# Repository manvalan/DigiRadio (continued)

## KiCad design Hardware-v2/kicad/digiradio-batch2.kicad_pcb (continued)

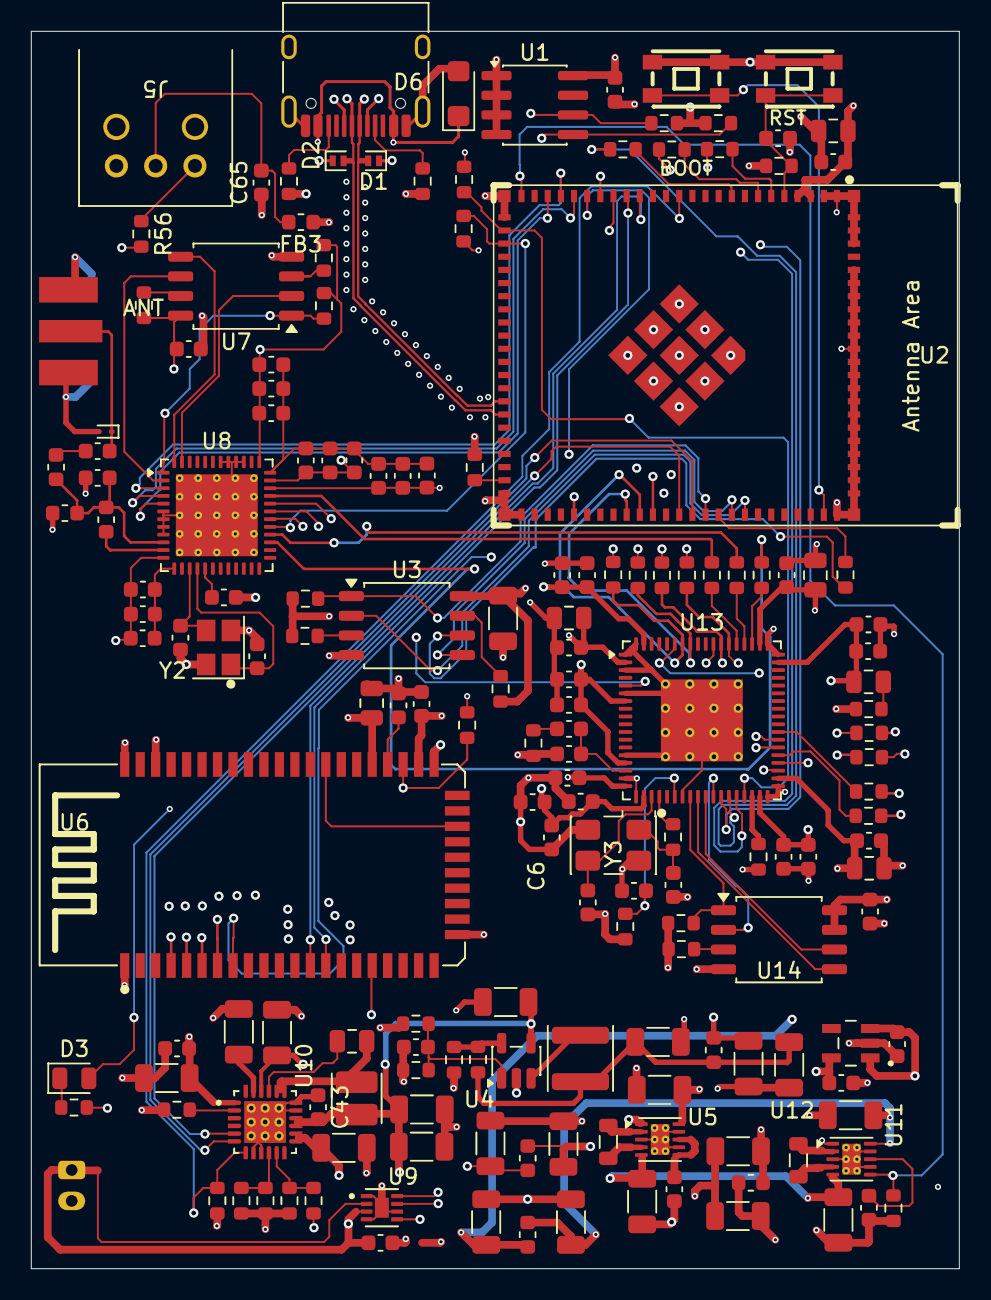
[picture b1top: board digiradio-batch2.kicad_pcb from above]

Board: 6 copper layers, 60.0 x 80.0 mm, 171 parts (1 on the bottom side), 119 nets.

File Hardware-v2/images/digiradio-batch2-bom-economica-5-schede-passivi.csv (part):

Riferimenti;Valore;Qta scheda;Qta necessaria;Stato;Fornitore;Codice;MPN scelto;Marca;Package;Stock;Pezzi da comprare;Prezzo unit EUR;Costo EUR;Costo originale EUR;Consegna;MPN schema;Impronta;Note;Opzioni da verificare
C1,C4,C15-C17,C19,C25,C32,C38,C44-C50,C54,C62-C65;100nF;21;105;Sostituito;LCSC;C282519;TCC0603X7R104K500CT;CCTC;0603;1010040;120;0,0055;0,6660;1,1099;;CC0603KRX7R9BB104;Capacitor_SMD:C_0603_1608Metric;;
C2,C6,C10,C24,C28,C31,C36,C37,C56,C57;1uF;10;50;Originale;LCSC;C5199872;CL10B105KB8NQNC;Samsung Electro-Mechanics;0603;2383870;50;0,0214;1,0696;1,0696;;CL10B105KB8NQNC;Capacitor_SMD:C_0603_1608Metric;;
C3;22uF;1;5;Sostituito;LCSC;C92814;LMK212BJ226MG-T;Taiyo Yuden;0805;6510;5;0,1156;0,5782;1,6756;;GRM21BZ71A226ME15L;Capacitor_SMD:C_0805_2012Metric;Su 3V3_DIGITAL. Gli alternativi sono X5R invece di X7R, che a 3,3 V va bene.;
C5,C9,C11,C12,C14,C42,C52,C55,C73-C76,C80,C83,C84;10uF;15;75;Sostituito;LCSC;C105482;1206X106K250NT;FH;1206;45370;80;0,0638;5,1056;15,2667;;CL31A106KBHNNNE;Capacitor_SMD:C_1206_3216Metric;Da 50 V a 25 V negli alternativi. La tensione più alta sulla riga è V_USB/PMID, 5 V.;
C8,C13,C33,C53;4.7uF;4;20;Sostituito;LCSC;C1872;CL31B475KAHNNNE;Samsung Electro-Mechanics;1206;60905;20;0,0577;1,1547;1,2621;;1206B475K500NT;Capacitor_SMD:C_1206_3216Metric;Da 50 V a 25 V con CL31B475KAHNNNE. La riga lavora su VSYS e REGN, massimo 5 V.;
C18,C58-C61;10uF;5;25;Sostituito;LCSC;C15850;CL21A106KAYNNNE;Samsung Electro-Mechanics;0805;1517320;40;0,0395;1,5789;2,1728;;GRM21BR61E106KA73L;Capacitor_SMD:C_0805_2012Metric;;
C20;33pF;1;5;Originale;LCSC;C913596;GQM1875C2E330JB12D;muRata;0603;790;5;0,1305;0,6525;0,6525;;GQM1875C2E330JB12D;Capacitor_SMD:C_0603_1608Metric;Rete di adattamento dell'antenna del Si4684: tengo il Murata ad alto Q, il risparmio è di centesimi.;C1663: C0G standard 50 V, Q più basso
C21,C26,C29,C34;8.2pF;4;20;Sostituito;LCSC;C376804;TCC0603COG8R2C500CT;CCTC;0603;1700;100;0,0038;0,3759;1,5217;;CC0603JRNPO9BN8R2;Capacitor_SMD:C_0603_1608Metric;;
C22;2.7pF;1;5;Originale;LCSC;C2178971;GQM1875C2E2R7BB12D;muRata;0603;1295;5;0,1421;0,7107;0,7107;;GQM1875C2E2R7BB12D;Capacitor_SMD:C_0603_1608Metric;Rete di adattamento dell'antenna del Si4684, tolleranza ±0,1 pF: tengo il Murata.;
C23,C27,C30,C35;2.2nF;4;20;Originale;LCSC;C16033;CL10B222KB8NNNC;Samsung Electro-Mechanics;0603;130050;50;0,0089;0,4431;0,4431;;CL10B222KB8NNNC;Capacitor_SMD:C_0603_1608Metric;;
C39;1nF;1;5;Sostituito;LCSC;C1588;CL10B102KB8NNNC;Samsung Electro-Mechanics;0603;1150850;50;0,0089;0,4431;0,7832;;GRM188R71H102KA01D;Capacitor_SMD:C_0603_1608Metric;;
C43;10uF;1;5;Sostituito;LCSC;C77044;GRM188R61A106KE69D;muRata;0603;198760;10;0,0306;0,3061;0,3831;;CL10A106KP8NNNC;Capacitor_SMD:C_0603_1608Metric;;
C51;47nF;1;5;Sostituito;LCSC;C282770;TCC0805X7R473K500DT;CCTC;0805;3400;50;0,0088;0,4386;0,7709;;CL21B473KBCNNNC;Capacitor_SMD:C_0805_2012Metric;Bootstrap del BQ25896. L'originale ha stock LCSC a zero.;
C67-C70;10nF;4;20;Originale;LCSC;C100042;CC0603KRX7R9BB103;YAGEO;0603;4000;100;0,0046;0,4565;0,4565;;CC0603KRX7R9BB103;Capacitor_SMD:C_0603_1608Metric;;
C79,C85;22uF;2;10;Sostituito;LCSC;C1859;1206X226K100NT;FH;1206;73980;10;0,1622;1,6219;2,1303;;CL31A226KAHNNNE;Capacitor_SMD:C_1206_3216Metric;Da 25 V a 10 V con 1206X226K100NT. La riga lavora sul lato 1,2 V.;
C81;150pF;1;5;Originale;LCSC;C107038;CC0603JRNPO9BN151;YAGEO;0603;328700;100;0,0046;0,4565;0,4565;;CC0603JRNPO9BN151;Capacitor_SMD:C_0603_1608Metric;;
C82;5.6nF;1;5;Sostituito;LCSC;C282685;TCC0603X7R562K500CT;CCTC;0603;4800;100;0,0030;0,3043;0,4475;;CC0603KRX7R9BB562;Capacitor_SMD:C_0603_1608Metric;;
C139-C142;12pF;4;20;Originale;LCSC;C107034;CC0603JRNPO9BN120;YAGEO;0603;1915200;100;0,0055;0,5550;0,5550;;CC0603JRNPO9BN120;Capacitor_SMD:C_0603_1608Metric;;
FB1-FB5;BLM18SG121TN1D;5;25;Sostituito;LCSC;C52178221;PBBHAQ1608H-121T30;PROD Tech;0603;4700;40;0,0215;0,8604;1,7633;;BLM18SG121TN1D;Inductor_SMD:L_0603_1608Metric;PROD Tech: stesso 120 Ω a 100 MHz e 3 A, DCR 50 mΩ contro 25 mΩ. Conviene solo da qualche scheda in su per il minimo d'ordine di 20.;
L1;18nH;1;5;Originale;LCSC;C113263;LQW18AN18NJ00D;muRata;0603;26020;10;0,0458;0,4583;0,4583;;LQW18AN18NJ00D;Inductor_SMD:L_0603_1608Metric;Rete RF del Si4684: tengo il Murata.;C6807995: APV AHW1608C-18NJTF, simile, Q 35
L2;120nH;1;5;Originale;LCSC;C341697;LQW18ANR12J00D;muRata;0603;105;5;0,1578;0,7890;0,7890;;LQW18ANR12J00D;Inductor_SMD:L_0603_1608Metric;Rete RF del Si4684: tengo il Murata. Stock LCSC basso.;C6364700: APV AHW1608C-R12JTF, simile, Q 32, SRF 1,3 GHz
L3;22nH;1;5;Sostituito;LCSC;C84341;LQW18AN22NG00D;muRata;0603;4230;10;0,0559;0,5594;0,5594;;LQW18AN22NH00D;Inductor_SMD:L_0603_1608Metric;L'originale ±3% non è a catalogo LCSC: uso la stessa serie Murata a ±2%.;
L4,L6;1.5uH;2;10;Originale;LCSC;C54421974;HPLA-201210-1R5-M;YOUCHI;0805;5980;20;0,0331;0,6616;0,6616;;HPLA-201210-1R5-M;Inductor_SMD:L_0805_2012Metric;;
L5;1uH;1;5;Originale;LCSC;C280505;LVF303015-1R0T-N;Chilisin;SMD,3x3mm;1600;10;0,0541;0,5406;0,5406;;LVF303015-1R0T-N;Inductor_SMD:L_Cenker_CKCS3015;;
L7;2.2uH;1;5;Sostituito;LCSC;C7427099;ANR4018T2R2M;APV;SMD,4x4mm;5230;10;0,0407;0,4073;0,4073;;SDER041H-2R2MS;Inductor_SMD:L_APV_ANR4018;L'originale Cyntec non è più acquistabile. APV ANR4018T2R2M è l'impronta già sul PCB: 2,6 A nominali e 3,2 A di saturazione, abbondanti per il buck da 1 A TLV62568.;
R1,R5,R9-R11,R14,R15,R17-R24,R26,R29,R31,R32,R34,R35,R54;10K;22;110;Sostituito;LCSC;C25804;0603WAF1002T5E;UNI-ROYAL;0603;3260200;200;0,0020;0,3938;0,4834;;RC0603FR-0710KL;Resistor_SMD:R_0603_1608Metric;;
R2,R3;5.1K;2;10;Sostituito;LCSC;C23186;0603WAF5101T5E;UNI-ROYAL;0603;16131200;100;0,0014;0,1432;0,1531;;FRC0603F5101TS;Resistor_SMD:R_0603_1608Metric;;
R7,R8;2.2K;2;10;Originale;LCSC;C4190;0603WAF2201T5E;UNI-ROYAL;0603;2719000;100;0,0016;0,1611;0,1611;;0603WAF2201T5E;Resistor_SMD:R_0603_1608Metric;;
R12;470;1;5;Originale;LCSC;C23179;0603WAF4700T5E;UNI-ROYAL;0603;1926400;100;0,0021;0,2059;0,2059;;0603WAF4700T5E;Resistor_SMD:R_0603_1608Metric;;
R16;560;1;5;Originale;LCSC;C2907052;FRC0603F5600TS;FOJAN;0603;900500;100;0,0015;0,1531;0,1531;;FRC0603F5600TS;Resistor_SMD:R_0603_1608Metric;;
R25;0.47;1;5;Originale;LCSC;C3013349;FRL0603FR470TS;FOJAN;0603;247300;100;0,0037;0,3656;0,3656;;FRL0603FR470TS;Resistor_SMD:R_0603_1608Metric;;
R27,R28;100K;2;10;Originale;LCSC;C25803;0603WAF1003T5E;UNI-ROYAL;0603;8712200;100;0,0027;0,2685;0,2685;;0603WAF1003T5E;Resistor_SMD:R_0603_1608Metric;;
R36-R45,R47-R50,R55,R56;33;16;80;Originale;LCSC;C23140;0603WAF330JT5E;UNI-ROYAL;0603;2013200;100;0,0021;0,2127;0,2127;;0603WAF330JT5E;Resistor_SMD:R_0603_1608Metric;;
R46;4.3k;1;5;Originale;LCSC;C2930099;FRC0603F4301TS;FOJAN;0603;901300;100;0,0018;0,1786;0,1786;;FRC0603F4301TS;Resistor_SMD:R_0603_1608Metric;;
R51;100;1;5;Originale;LCSC;C105588;RC0603FR-07100RL;YAGEO;0603;723800;100;0,0017;0,1701;0,1701;;RC0603FR-07100RL;Resistor_SMD:R_0603_1608Metric;;
R52;220;1;5;Originale;LCSC;C22962;0603WAF2200T5E;UNI-ROYAL;0603;1340100;100;0,0017;0,1684;0,1684;;0603WAF2200T5E;Resistor_SMD:R_0603_1608Metric;;
R53;1K;1;5;Sostituito;LCSC;C21190;0603WAF1001T5E;UNI-ROYAL;0603;5489700;100;0,0015;0,1522;0,3222;;RC0603FR-071KL;Resistor_SMD:R_0603_1608Metric;;
Y2;ABM8-19.200MHZ-10-1-U-T;1;5;Originale;Mouser;ABM8-19.200MHZ-10-1-U-T;ABM8-19.200MHZ-10-1-U-T;Abracon;;3469;5;0,4210;2,1050;2,1050;;ABM8-19.200MHZ-10-1-U-T;Crystal:Crystal_SMD_Abracon_ABM8AIG-4Pin_3.2x2.5mm;Quarzo del Si4684, già calibrato su v1. Il risparmio con i cinesi è minimo, quindi tengo Abracon.;"C718671: LIMING ±10 ppm 10 pF, ESR non pubblicata; C7302008: SCTF ±10 ppm, stabilità ±30 ppm, ESR 60 Ω"
Y3;ABM3B-12.288MHZ-10-1-U-T;1;5;Originale;Mouser;ABM3B-12.288MHZ-10-1-U-T;ABM3B-12.288MHZ-10-1-U-T;Abracon;;305;5;0,6710;3,3550;3,3550;;ABM3B-12.288MHZ-10-1-U-T;Crystal:Crystal_SMD_5032-4Pin_5.0x3.2mm;Clock dell'ADAU1452, con C141/C142 da 12 pF calcolati su CL 10 pF.;C557167: SJK 10 pF, ±20 ppm, ESR non pubblicata: controlla che rientri nelle specifiche ADAU1452
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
